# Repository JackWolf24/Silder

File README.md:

## Camera Slider 
Dieses Projekt ist ein Schittmotor betriebener Camera Slider.
Dieser kann eine Kamera von max 1,5kg Vertikal, über bestimmten Zeitraum, entlang einer Achse linear bewegen.
Es ist im gesamten eine alukonstruktion von 1,25m länge, die Eigens angefertigte PCBs zur elektronischen Verschaltung verwendet.
Die Eingabe der Zielzeit erfolgt über rotary encoder und die Anzeige über ein 1,9" TFT Display. Gesteuert wird alles das mit einem Arduino Nano.

## Eindrücke
# CAD

# PCB

Das Projekt befindet sich in den Vollendung.

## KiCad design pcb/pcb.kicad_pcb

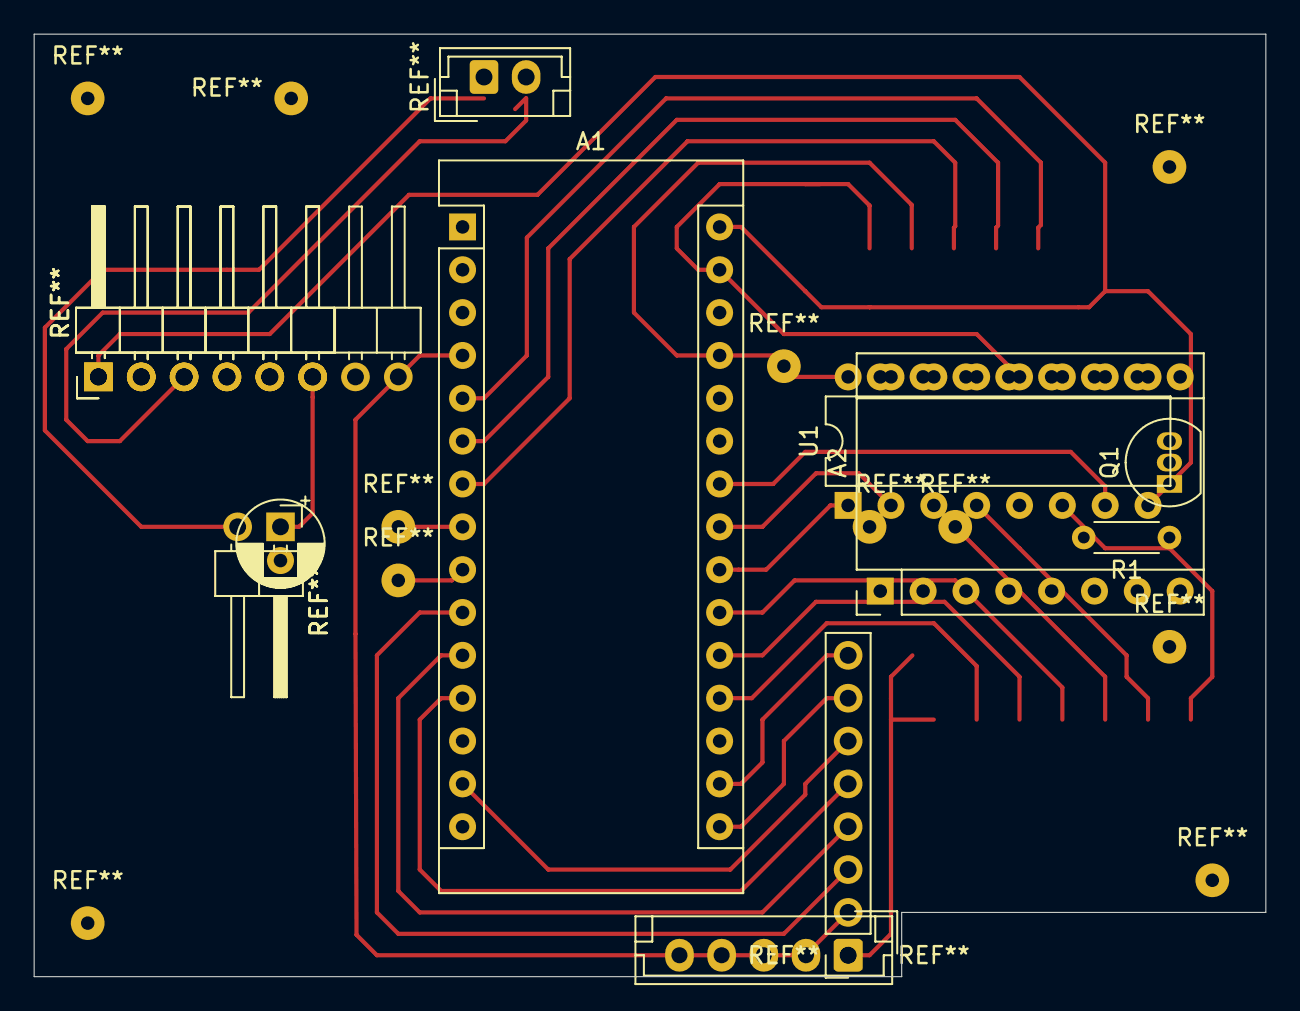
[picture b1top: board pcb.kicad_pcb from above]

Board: 2 copper layers, 73.0 x 55.9 mm, 5 parts (0 on the bottom side), 8 nets.

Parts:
A1: Nano_v3.x; Arduino_Nano
A2: A4988; Pololu_Breakout-16_15.2x20.3mm
Q1: 2N3906; TO-92_Inline
R1: R; R_Axial_DIN0204_L3.6mm_D1.6mm_P5.08mm_Horizontal
U1: L293D; DIP-16_W7.62mm

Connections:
unnamed: A2.9, Q1.2, R1.2
unnamed: A1.22, U1.1
unnamed: A1.23, A2.15, U1.2
unnamed: A1.24, A2.16, U1.7
unnamed: A2.13, A2.14
ardu_5V: A1.27, A2.2, A2.10, A2.11, A2.12, Q1.3, U1.16
ardu_gnd: A1.29, A2.7, Q1.1, R1.1, U1.12
ardu_vcc: A1.30, A2.8, U1.8

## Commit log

2021-04-11 initial V2
2021-04-11 hallo
2021-09-05 update v3
2021-09-13 del file in worng branch
2021-10-11 add pcb
2021-10-14 add display support
2021-10-17 update pcb
2021-10-25 update cad structure, pcb mounting holes, display mounting holes
2021-10-28 add l293d test
2021-10-29 replace a4899 with l2903d; resolve merge conflicts
2021-10-29 add zeitrechner table
2021-11-02 fix stash conflicts
2021-11-02 added l293d en / PWM pin connection
2021-11-06 general update
